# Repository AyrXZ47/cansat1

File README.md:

# cansat1
Codigo de la nueva version del Tuzo Cansat AEM-UAZ

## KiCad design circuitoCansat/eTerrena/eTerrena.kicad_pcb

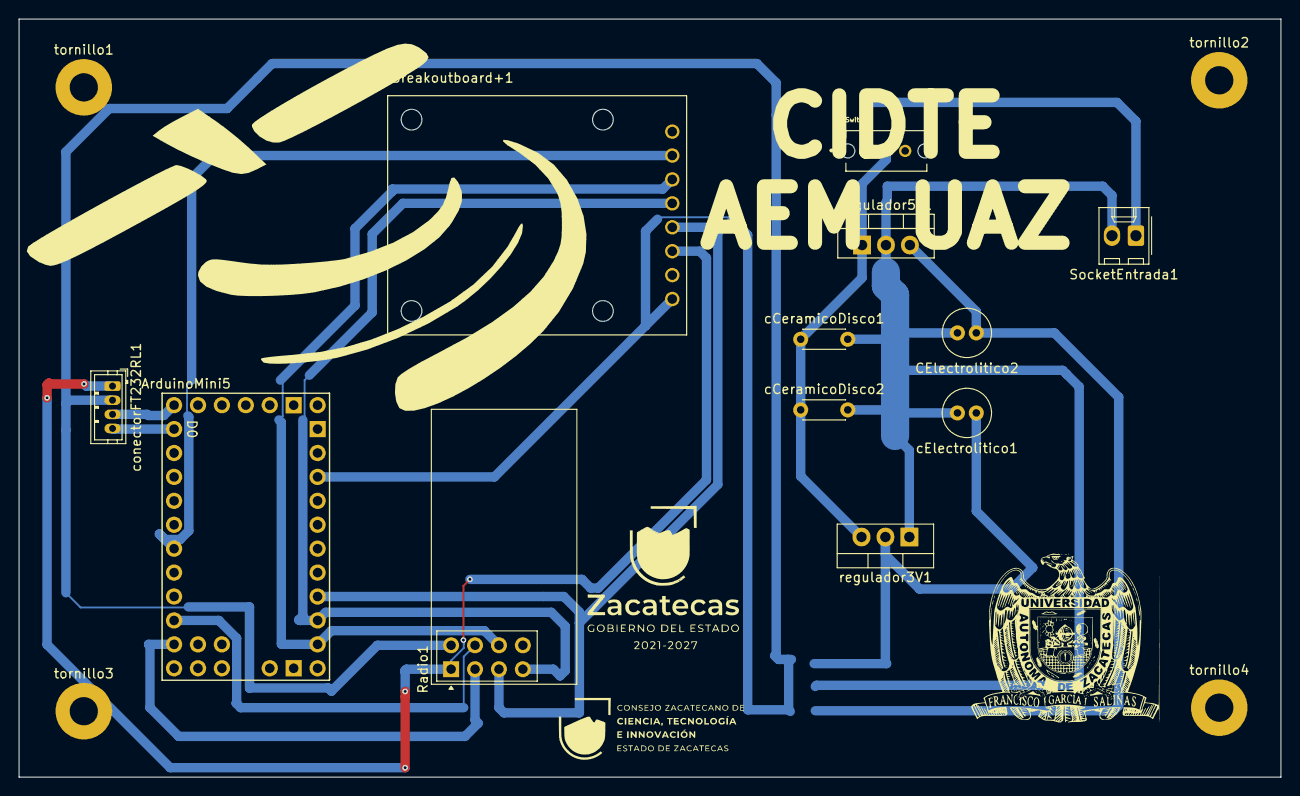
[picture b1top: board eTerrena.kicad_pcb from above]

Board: 2 copper layers, 134.0 x 80.5 mm, 16 parts (0 on the bottom side), 14 nets.

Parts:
ArduinoMini5: Arduino_101_Shield; Arduino_Mini_Socket
CElectrolitico2: 4.7uf 63v; C_Radial_D5.0mm_H11.0mm_P2.00mm
Radio1: NRF24L01_Breakout; nRF24L01_Breakout
SocketEntrada1: Conn_01x02_Socket; Molex_KK-254_AE-6410-02A_1x02_P2.54mm_Vertical
Switch1: OS102011MS2QN1; SW_OS102011MS2QN1
cCeramicoDisco1, cCeramicoDisco2: 0.1 uf; C_Disc_D4.3mm_W1.9mm_P5.00mm
cElectrolitico1: 4.7uf 63v; C_Radial_D5.0mm_H11.0mm_P2.00mm
conectorFT232RL1: Conn_01x04_Socket; JST_ZH_B4B-ZR_1x04_P1.50mm_Vertical
microSDBreakoutboard+1: microSDBreakoutBoard+; MODULE_254
regulador3V1: LD33V; TO-220-3_Vertical
regulador5v1: L7805; TO-220-3_Vertical
tornillo1, tornillo2, tornillo3, tornillo4: MountingHole_3mm_Pad

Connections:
3.3v: cElectrolitico1.1, regulador3V1.2 (Vout)
5v: CElectrolitico2.1, regulador5v1.3 (OUT)
+3.3V: ArduinoMini5.5V1 (5V), Radio1.2 (VCC), conectorFT232RL1.2, microSDBreakoutboard+1.8 (5V)
+9V: SocketEntrada1.1, Switch1.1
GND: CElectrolitico2.2, Radio1.1 (GND), SocketEntrada1.2, cCeramicoDisco1.2, cCeramicoDisco2.2, cElectrolitico1.2, conectorFT232RL1.1, microSDBreakoutboard+1.6 (GND), regulador3V1.1 (GND), regulador5v1.2 (GND)
unnamed: ArduinoMini5.D8, Radio1.3 (CE)
unnamed: ArduinoMini5.D12, Radio1.7 (MISO), microSDBreakoutboard+1.4 (DO)
unnamed: ArduinoMini5.D11, Radio1.6 (MOSI), microSDBreakoutboard+1.3 (DI)
unnamed: ArduinoMini5.D13, Radio1.5 (SCK), microSDBreakoutboard+1.5 (CLK)
unnamed: ArduinoMini5.D7, Radio1.4 (~CSN)
unnamed: ArduinoMini5.D4, microSDBreakoutboard+1.2 (CS)
unnamed: Switch1.2, cCeramicoDisco1.1, cCeramicoDisco2.1, regulador3V1.3 (Vin), regulador5v1.1 (IN)
RX FT232RL: ArduinoMini5.D1 (D1/TX), conectorFT232RL1.4
TX FT232RL: ArduinoMini5.D0 (D0/RX), conectorFT232RL1.3

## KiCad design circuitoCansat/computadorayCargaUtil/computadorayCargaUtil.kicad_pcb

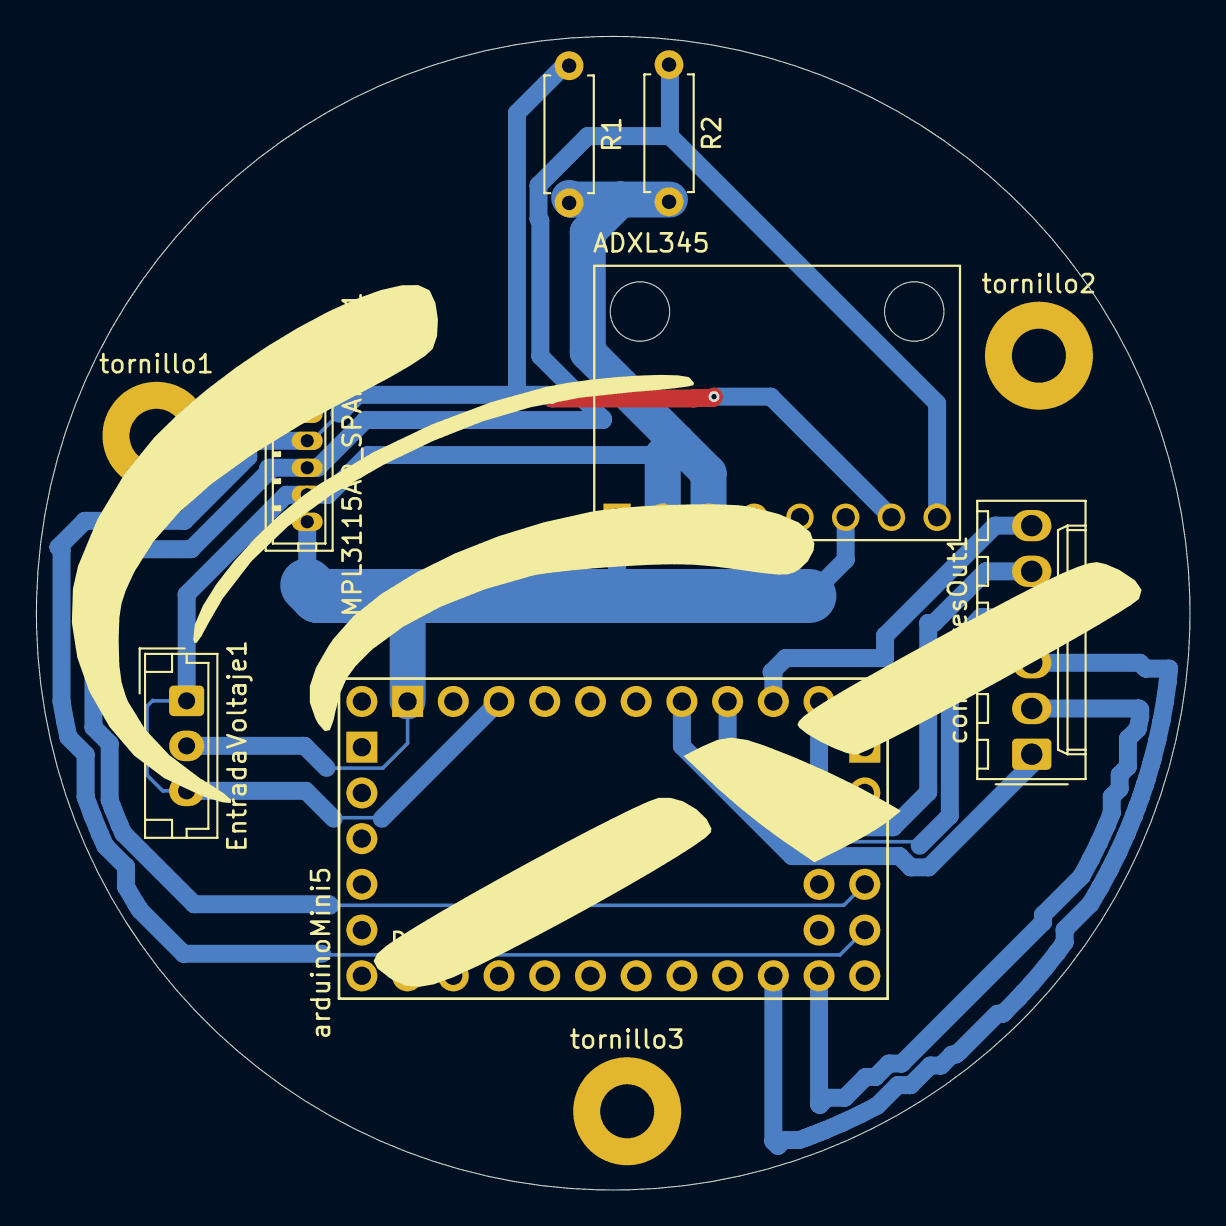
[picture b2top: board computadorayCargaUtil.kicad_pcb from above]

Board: 2 copper layers, 64.1 x 64.1 mm, 10 parts (0 on the bottom side), 10 nets.

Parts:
ADXL345: SEN-09836; MODULE_SEN-09836
EntradaVoltaje1: Conn_01x03_Pin; JST_EH_B3B-EH-A_1x03_P2.50mm_Vertical
MPL3115A2_SPARKFUN1: Conn_01x06_Socket; JST_ZH_B6B-ZR_1x06_P1.50mm_Vertical
R1, R2: 1k ohm; R_Axial_DIN0207_L6.3mm_D2.5mm_P7.62mm_Horizontal
arduinoMini5: Arduino_101_Shield; Arduino_Mini_Socket
conectoresOut1: Conn_01x06_Pin; Molex_KK-254_AE-6410-06A_1x06_P2.54mm_Vertical
tornillo1, tornillo2, tornillo3: MountingHole_3mm_Pad

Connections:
+3.3V: ADXL345.2 (VCC), ADXL345.3 (CS), EntradaVoltaje1.1, EntradaVoltaje1.3, MPL3115A2_SPARKFUN1.5, R1.2, R2.2, arduinoMini5.5V1 (5V)
GND: ADXL345.1 (GND), ADXL345.6 (SDO), EntradaVoltaje1.2, MPL3115A2_SPARKFUN1.6, arduinoMini5.GND2 (GND)
unnamed: ADXL345.8 (SCL), MPL3115A2_SPARKFUN1.4, R2.1, arduinoMini5.A5
unnamed: ADXL345.7 (SDA), MPL3115A2_SPARKFUN1.3, R1.1, arduinoMini5.A4
ceRadio: arduinoMini5.D8, conectoresOut1.2
csnRadio: arduinoMini5.D7, conectoresOut1.3
misoRadio: arduinoMini5.D12, conectoresOut1.6
mosiRadio: arduinoMini5.D11, conectoresOut1.5
pata2tmp36gz: arduinoMini5.A0, conectoresOut1.1
sckRadio: arduinoMini5.D13, conectoresOut1.4

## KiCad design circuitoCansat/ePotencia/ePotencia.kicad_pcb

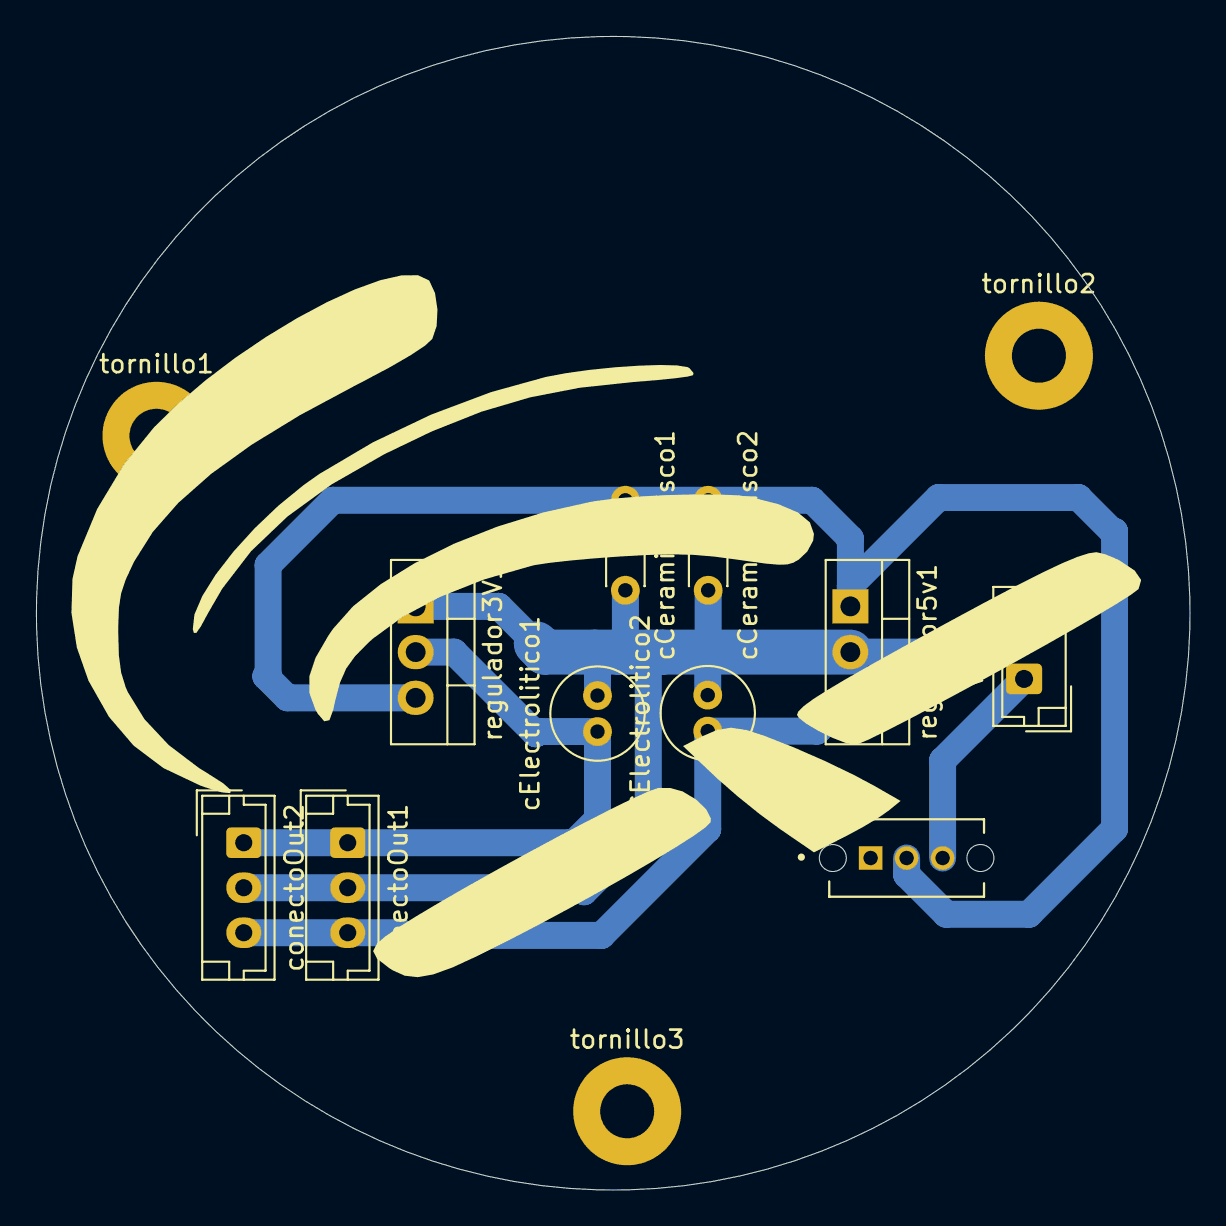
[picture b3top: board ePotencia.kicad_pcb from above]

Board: 2 copper layers, 64.1 x 64.1 mm, 13 parts (0 on the bottom side), 5 nets.

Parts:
CElectrolitico2: 4.7uf 63v; C_Radial_D5.0mm_H11.0mm_P2.00mm
Switch1: OS102011MS2QN1; SW_OS102011MS2QN1
Vcc1: Conn_01x02_Pin; JST_EH_B2B-EH-A_1x02_P2.50mm_Vertical
cCeramicoDisco1, cCeramicoDisco2: 0.1 uf; C_Disc_D4.3mm_W1.9mm_P5.00mm
cElectrolitico1: 4.7uf 63v; C_Radial_D5.0mm_H11.0mm_P2.00mm
conectoOut1, conectoOut2: Conn_01x03_Pin; JST_EH_B3B-EH-A_1x03_P2.50mm_Vertical
regulador3V1: LD33V; TO-220-3_Vertical
regulador5v1: L7805; TO-220-3_Vertical
tornillo1, tornillo2, tornillo3: MountingHole_3mm_Pad

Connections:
3.3v: cElectrolitico1.1, conectoOut1.1, conectoOut2.1, regulador3V1.2 (Vout)
5v: conectoOut1.3, conectoOut2.3
+9V: Switch1.3, Vcc1.1
GND: CElectrolitico2.2, Vcc1.2, cCeramicoDisco1.2, cCeramicoDisco2.2, cElectrolitico1.2, conectoOut1.2, conectoOut2.2, regulador3V1.1 (GND), regulador5v1.2 (GND)
unnamed: Switch1.2, cCeramicoDisco1.1, cCeramicoDisco2.1, regulador3V1.3 (Vin), regulador5v1.1 (IN)

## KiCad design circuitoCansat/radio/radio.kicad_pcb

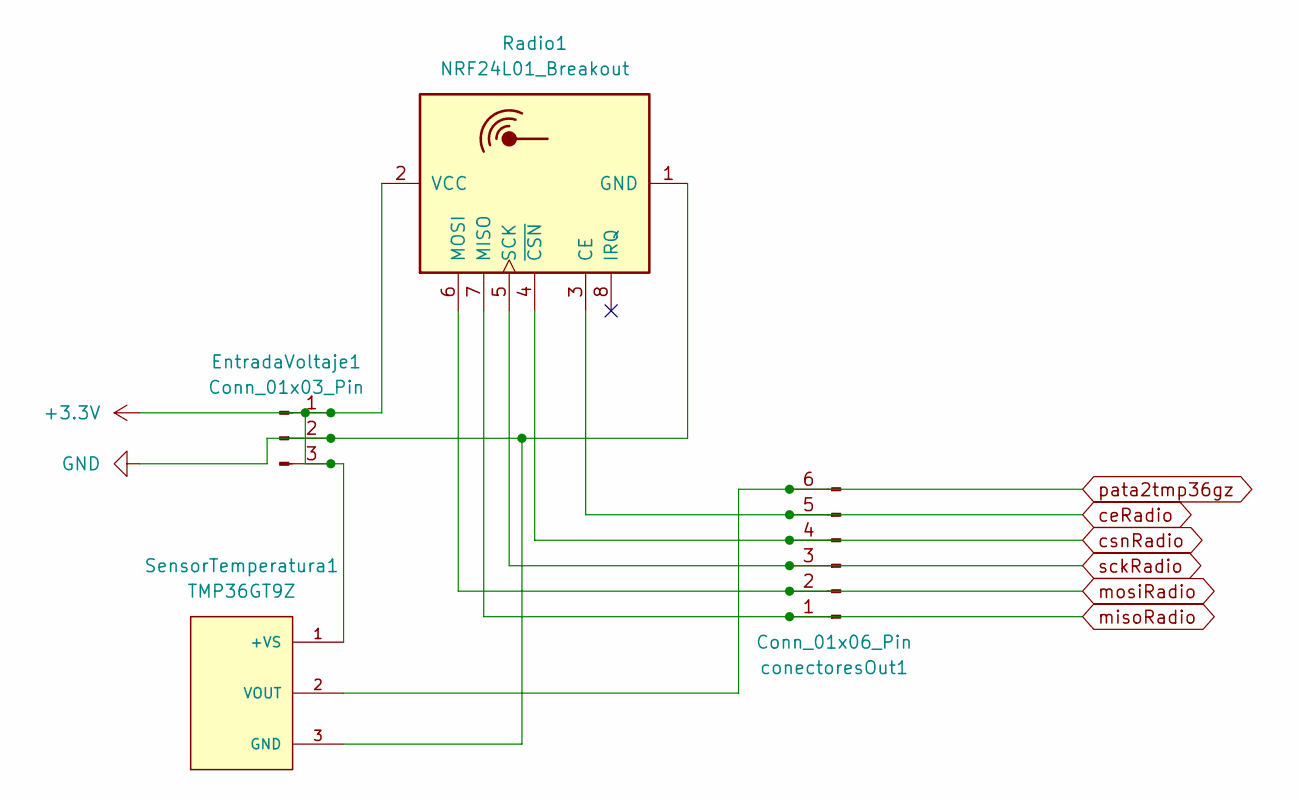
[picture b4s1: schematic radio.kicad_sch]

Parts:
EntradaVoltaje1: Conn_01x03_Pin; JST_EH_B3B-EH-A_1x03_P2.50mm_Vertical
Radio1: NRF24L01_Breakout; nRF24L01_Breakout
SensorTemperatura1: TMP36GT9Z; TO-92; PARTREV H
conectoresOut1: Conn_01x06_Pin; Molex_KK-254_AE-6410-06A_1x06_P2.54mm_Vertical

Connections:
+3.3V: EntradaVoltaje1.1, EntradaVoltaje1.3, Radio1.2 (VCC), SensorTemperatura1.1 (+VS)
GND: EntradaVoltaje1.2, Radio1.1 (GND), SensorTemperatura1.3 (GND)
ceRadio: Radio1.3 (CE), conectoresOut1.5
csnRadio: Radio1.4 (~CSN), conectoresOut1.4
misoRadio: Radio1.7 (MISO), conectoresOut1.1
mosiRadio: Radio1.6 (MOSI), conectoresOut1.2
pata2tmp36gz: SensorTemperatura1.2 (VOUT), conectoresOut1.6
sckRadio: Radio1.5 (SCK), conectoresOut1.3

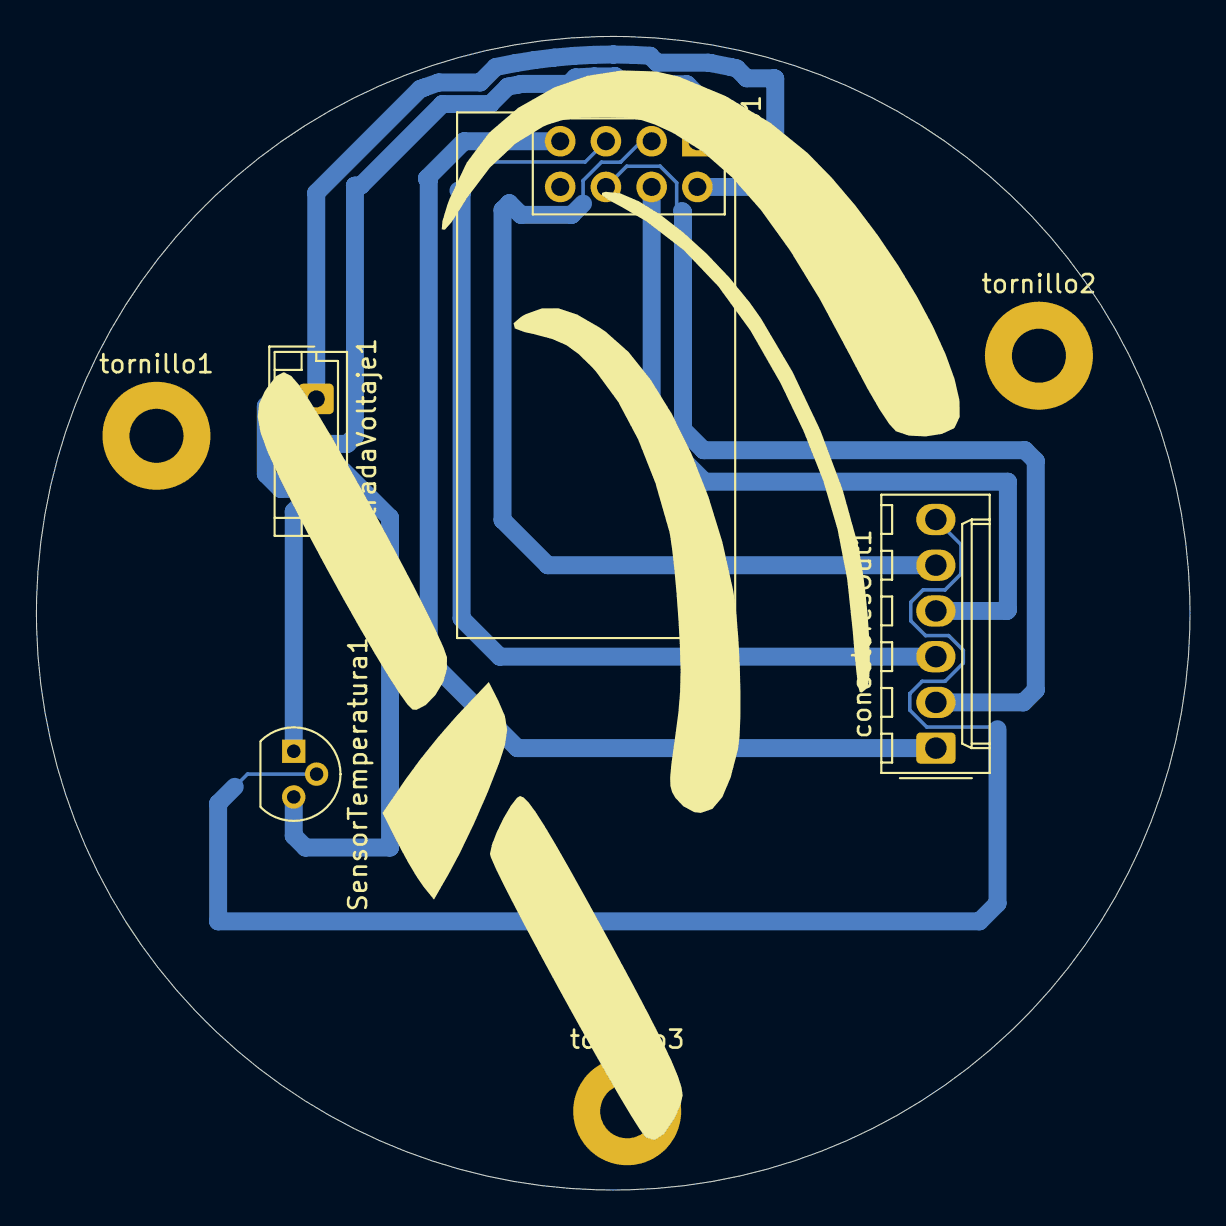
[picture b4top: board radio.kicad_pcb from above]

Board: 2 copper layers, 64.1 x 64.1 mm, 7 parts (0 on the bottom side), 8 nets.

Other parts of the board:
tornillo1, tornillo2, tornillo3: MountingHole_3mm_Pad

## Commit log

2024-06-27 Codigo para plataforma Arduino
2024-06-27 Código para GUI de CANSAT
2024-06-27 Arreglar declaraciones de modulos
2024-06-28 Añadir logica para realizar handshake (sin probar aun)
2024-06-28 Crear archivo de configuración
2024-06-28 Centrar ventana al abrir
2024-06-28 Añadida ventana de conexión
2024-06-28 Añadir evento de conexión
2024-07-03 Añadir ventana de espera del CANSAT
2024-07-03 Se cambió la ventana de espera a un dialogo de progreso
2024-07-03 Añadir declaracioón de paquetes
2024-07-03 El dialogo de conexión ya no aparece aleatoriamente
2024-07-03 Añadir plantilla para realizar graficas
2024-07-04 Mover valores de graficas a la clase constantes
2024-07-04 Añadir diagrama de clases
2024-07-04 Añadir anotación en configuracion
2024-07-04 Refactor en grafica, ahora toma los valores de constants.py
2024-07-04 Ahora se abre el programa desde la ventana de conexion
2024-07-04 Se eliminó el campo de lenguaje de la configuración
2024-07-04 Añadir vista para modelo 3D
2024-07-04 Añadir requerimientos nuevos
2024-07-04 Se añade el visor para el modelo 3D.
2024-07-04 Se movieron los valores del visor a la clase constantes
2024-07-04 REORGANIZAR ARCHIVO DE CONSTANTES
2024-07-05 Añadir señal para recibir datos del arduino en la interfaz
2024-07-05 Ahora la interfaz muestra mensajes de error en caso de que la estación terrena no se inicialice correctamente, asi como mensajes de progreso
2024-07-05 Eliminado dialogo sin usar
2024-07-05 Ahora la ventana principal muestra el estado de la estacion terrena
2024-07-05 Ahora las graficas muestran la información proveniente del CanSat
2024-07-07 AHORA SE CALCULAN LOS GRADOS DE INCLINACION SEGUN DATOS DEL ACELEROMETRO
2024-07-08 Ahora es posible rotar el modelo
2024-07-08 Ahora el modelo 3D rota según la orientacion del CanSat
2024-07-08 Ahora hay mensaje de error si ocurre un error de comunicacion.
2024-07-08 LIMPIEZA Y ORGANIZACION DE CODIGO EXISTENTE
2024-07-08 Se cambiaron textos por constantes.
2024-07-08 Arreglado error con la constante de la velocidad
2024-07-08 Se añade licencia al codigo fuente
2024-07-08 Ahora las graficas muestran diferentes colores, se agrega grafica para datos del acelerometro
2024-07-08 Ahora es posible cambiar el color de fondo del modelo 3D
2024-07-08 Arreglar sentencias de importacion
2024-07-08 Falto el del main :p
2024-07-08 Corregir ruta de acceso del modelo 3D
2024-07-08 Agregar modelo 3D provisional
2024-07-09 Anadir modo DEBUG
2024-07-09 Ahora es posible mostrar y ocultar las graficas
2024-07-09 Si se produce un error de comunicacion, se muestra un mensaje de error
2024-07-09 Si se produce un error de comunicacion al momento de la conexion, ahora se cierra el dialgo de progreso
2024-07-09 Ahora si hay un error al iniciar la comunicacion, se muestra un mensaje de error
2024-07-09 Ahora se reinicia la aplicacion si hay un error de comunicacion durante la visualizacion
2024-07-09 Añadir boton de volver
2024-07-09 Añadir boton de configuracion
2024-07-10 Eliminar elementos de configuracion
2024-07-10 Añadir modelo 3D definitivo, añadir icono para Mac
2024-07-10 Mejorar icono para mac
2024-07-10 Si sucede un error de inicializacion cuando esta abierta la visualizacion, vuelve a la ventana de conexion
2024-07-10 Ahora se muestran mensajes de error explicitos
2024-07-10 Ahora el hilo de comunicacion se cierra antes de mostrar el mensaje de error para evitar duplicados
2024-07-10 Agregar comando para empaquetar en windows
2024-07-10 Modificar envio de datos por puerto serie
2024-07-10 Reorganizar codigo de ventana de conexion
2024-07-10 Reorganizar codigo de ventana principal
2024-07-11 Aplicar estilo a interfaz de monitoreo
2024-07-11 Aplicar titulo a graficas
2024-07-11 AHORA ES POSIBLE CONFIGURAR PARAMETROS VISUALES DESDE CONSTANTS.PY
2024-07-11 Cambiar esquema de colores
2024-07-11 Se agrega titulo a labels de acelaracion, temperatura, altitud y presion, eliminar imports inecesarios
2024-07-11 Agregar comentarios extra al codigo
2024-07-11 Arreglar congelamiento al volver a la ventana de conexion, corregir rotacion del modelo 3D
2024-07-11 Posible arreglo de error termios
2024-07-11 Arreglar modo DEBUG
2024-07-15 Corregir archivo requierements y comandos de empaquetamiento
2024-07-15 Actualizar README.md
2024-07-17 Renombrar programa
2024-07-18 Agregar labels a grafica de aceleracion
2024-08-12 actualizacion en circuitos y orden de carpetas
2024-08-12 placa de logos
